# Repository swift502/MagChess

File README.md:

# MagChess

Magnetic chess game interpreter and PGN exporter for the Lego [Traditional Chess Set](https://www.lego.com/en-cz/product/traditional-chess-set-40719). Python app for the Raspberry Pi, and an Astro website to serve the results and show a leaderboard.

## App

**Setup:**

```bash
rpi_install.sh
```

After installation, a reboot is required for the I2C data rate change to take effect.

**Run:**

```bash
rpi_run.sh
```

### Desktop shortcut

```ini
[Desktop Entry]
Type=Application
Name=MagChess
Icon=/home/pi/Documents/Github/MagChess/app/assets/icon.ico
Exec=/home/pi/Documents/Github/MagChess/app/rpi_run.sh
Category=Game
```

### Autostart config

```bash
mkdir -p ~/.config/autostart
nano ~/.config/autostart/magchess.desktop
```

## Hardware

The PCB in `kicad/pcb` is designed to fit a modified underside of the lego chessboard construction found in `bricklink_studio/chessboard.io`.

The PCB needs the following components soldered onto it:

- 64x SS49E
- 4x CD74HC4067
- ADS1015
- MP1584EN

Each lego chess piece has to be fitted with a magnet on the bottom. Round 5x2mm magnets happen to fit perfectly into the bottom of each piece.

Magnet polarity is important, if white pieces read magnetic north, black pieces should be flipped and read south. The hall sensors will then read colors as positive/negative voltage, which gives the app enough information to interpret chess moves correctly.

The app should be installed on a Raspberry Pi. The chessboard draws 5V and GND from the pi. Data pins are the I2C SDA and SCL pins and four mux selection pins, by default D21, D20, D16 and D12. An estimated 800mA is drawn by the hall sensors when powered.

## Scoreboard

<div align="center">
    <a href="https://swift502.github.io/MagChess">https://swift502.github.io/MagChess</a>
</div>
<br>

Astro website showing a leaderboard and a PGN archive. Deployed via GitHub Pages.

### Build notes

```bash
npm install
npm run dev
npm run build
```

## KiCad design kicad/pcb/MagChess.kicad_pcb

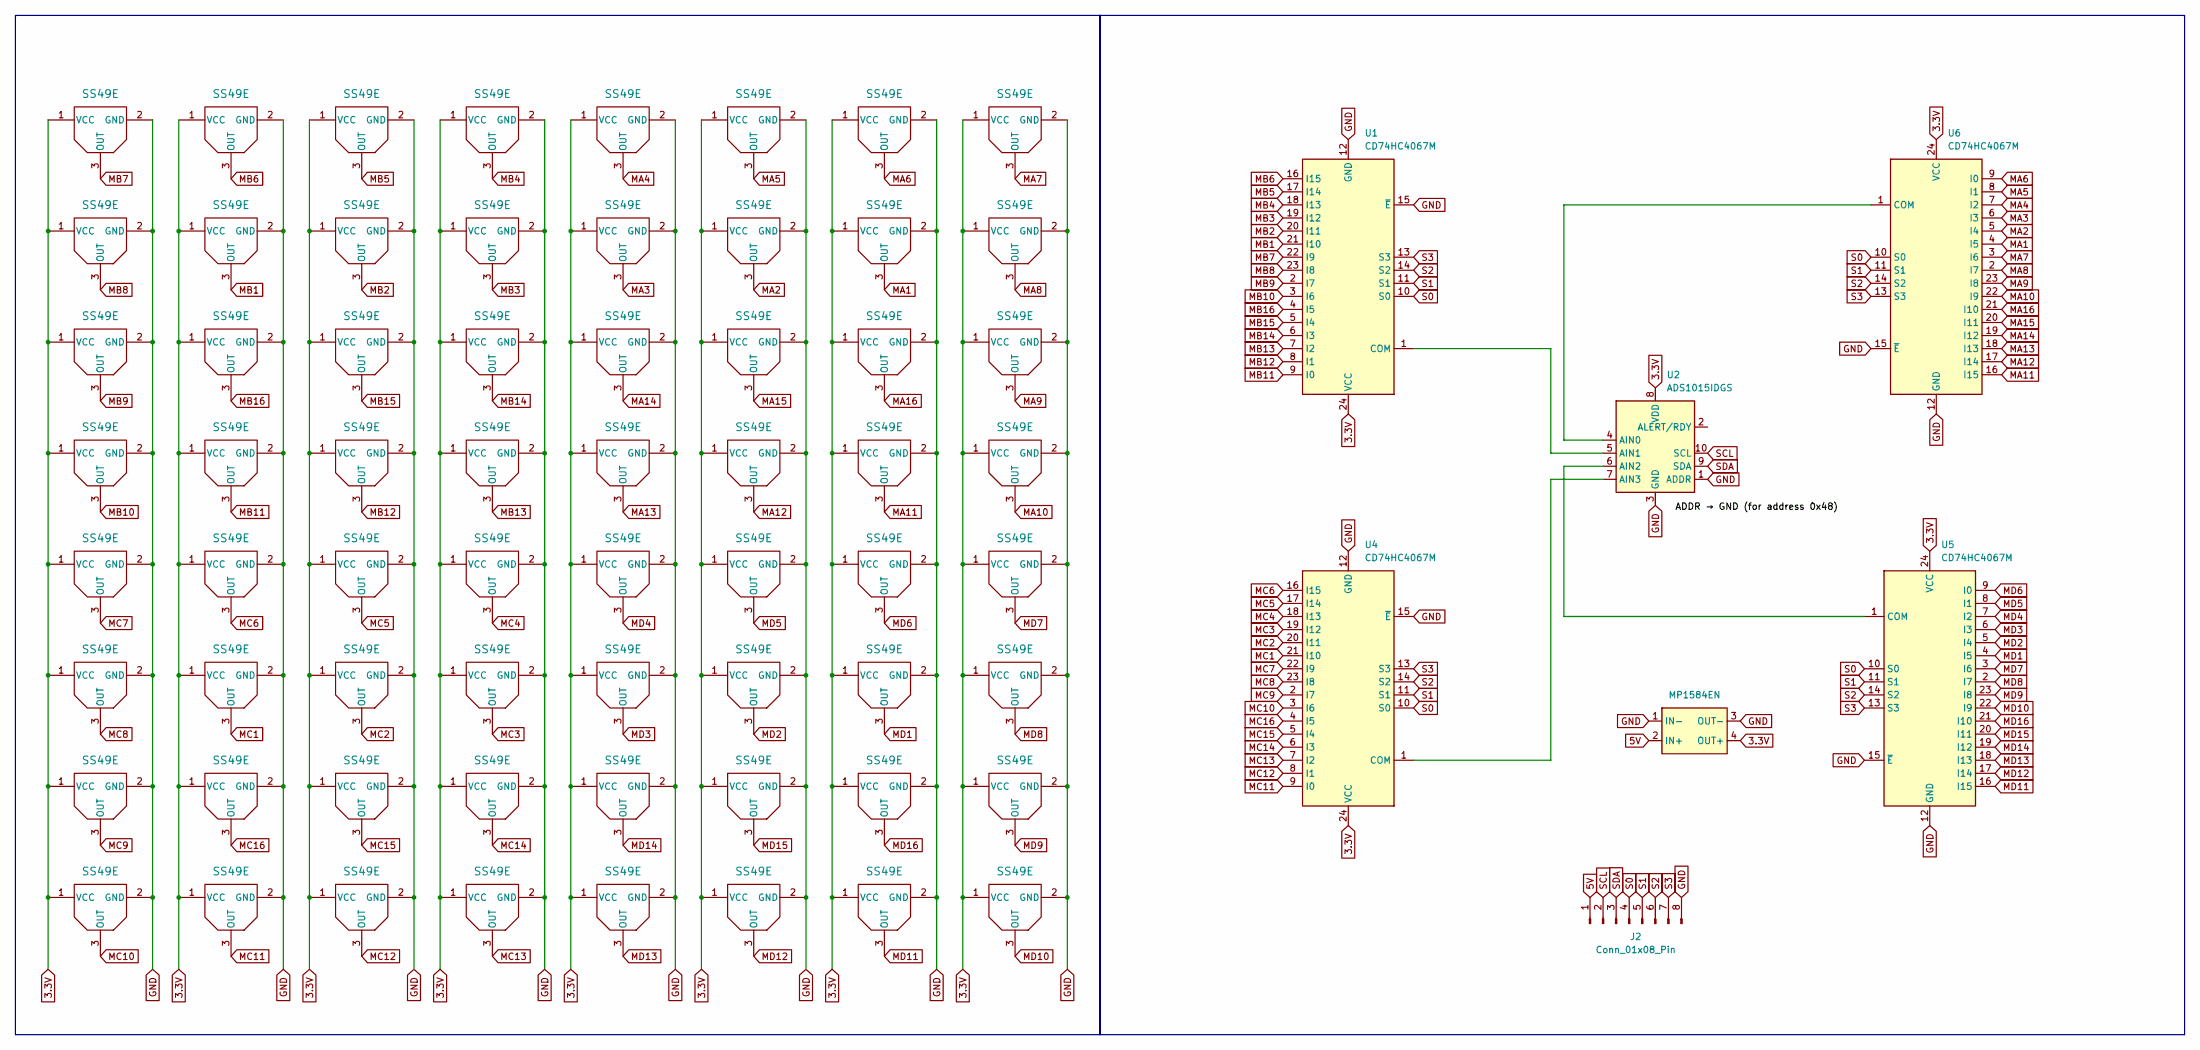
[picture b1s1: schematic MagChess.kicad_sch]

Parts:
J2: Conn_01x08_Pin; PinHeader_1x08_P2.54mm_Vertical
U1, U4, U5, U6: CD74HC4067M; CD74HC4067
U2: ADS1015IDGS; ADS1015
U3: MP1584EN; MP1584
U12, U13, U14, U15, U16, U17, U18, U19, U20, U21, U22, U23, U24, U25, U26, U27, U28, U29, U30, U31, U32, U33, U34, U35, U36, U37, U38, U39, U40, U41, U42, U43, U44, U45, U46, U47, U48, U49, U50, U51, U52, U53, U54, U55, U56, U57, U58, U59, U60, U61, U62, U63, U64, U65, U66, U67, U68, U69, U70, U71, U72, U73, U74, U75: SS49E

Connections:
3.3V: U1.24 (VCC), U2.8 (VDD), U3.4 (OUT+), U4.24 (VCC), U5.24 (VCC), U6.24 (VCC), U12.1 (VCC), U13.1 (VCC), U14.1 (VCC), U15.1 (VCC), U16.1 (VCC), U17.1 (VCC), U18.1 (VCC), U19.1 (VCC), U20.1 (VCC), U21.1 (VCC), U22.1 (VCC), U23.1 (VCC), U24.1 (VCC), U25.1 (VCC), U26.1 (VCC), U27.1 (VCC), U28.1 (VCC), U29.1 (VCC), U30.1 (VCC), U31.1 (VCC), U32.1 (VCC), U33.1 (VCC), U34.1 (VCC), U35.1 (VCC), U36.1 (VCC), U37.1 (VCC), U38.1 (VCC), U39.1 (VCC), U40.1 (VCC), U41.1 (VCC), U42.1 (VCC), U43.1 (VCC), U44.1 (VCC), U45.1 (VCC), U46.1 (VCC), U47.1 (VCC), U48.1 (VCC), U49.1 (VCC), U50.1 (VCC), U51.1 (VCC), U52.1 (VCC), U53.1 (VCC), U54.1 (VCC), U55.1 (VCC), U56.1 (VCC), U57.1 (VCC), U58.1 (VCC), U59.1 (VCC), U60.1 (VCC), U61.1 (VCC), U62.1 (VCC), U63.1 (VCC), U64.1 (VCC), U65.1 (VCC), U66.1 (VCC), U67.1 (VCC), U68.1 (VCC), U69.1 (VCC), U70.1 (VCC), U71.1 (VCC), U72.1 (VCC), U73.1 (VCC), U74.1 (VCC), U75.1 (VCC)
5V: J2.1, U3.2 (IN+)
GND: J2.8, U1.12 (GND), U1.15 (~E), U2.1 (ADDR), U2.3 (GND), U3.1 (IN-), U3.3 (OUT-), U4.12 (GND), U4.15 (~E), U5.12 (GND), U5.15 (~E), U6.12 (GND), U6.15 (~E), U12.2 (GND), U13.2 (GND), U14.2 (GND), U15.2 (GND), U16.2 (GND), U17.2 (GND), U18.2 (GND), U19.2 (GND), U20.2 (GND), U21.2 (GND), U22.2 (GND), U23.2 (GND), U24.2 (GND), U25.2 (GND), U26.2 (GND), U27.2 (GND), U28.2 (GND), U29.2 (GND), U30.2 (GND), U31.2 (GND), U32.2 (GND), U33.2 (GND), U34.2 (GND), U35.2 (GND), U36.2 (GND), U37.2 (GND), U38.2 (GND), U39.2 (GND), U40.2 (GND), U41.2 (GND), U42.2 (GND), U43.2 (GND), U44.2 (GND), U45.2 (GND), U46.2 (GND), U47.2 (GND), U48.2 (GND), U49.2 (GND), U50.2 (GND), U51.2 (GND), U52.2 (GND), U53.2 (GND), U54.2 (GND), U55.2 (GND), U56.2 (GND), U57.2 (GND), U58.2 (GND), U59.2 (GND), U60.2 (GND), U61.2 (GND), U62.2 (GND), U63.2 (GND), U64.2 (GND), U65.2 (GND), U66.2 (GND), U67.2 (GND), U68.2 (GND), U69.2 (GND), U70.2 (GND), U71.2 (GND), U72.2 (GND), U73.2 (GND), U74.2 (GND), U75.2 (GND)
MA1: U6.4 (I5), U21.3 (OUT)
MA2: U6.5 (I4), U31.3 (OUT)
MA3: U6.6 (I3), U32.3 (OUT)
MA4: U6.7 (I2), U29.3 (OUT)
MA5: U6.8 (I1), U28.3 (OUT)
MA6: U6.9 (I0), U20.3 (OUT)
MA7: U6.3 (I6), U12.3 (OUT)
MA8: U6.2 (I7), U13.3 (OUT)
MA9: U6.23 (I8), U14.3 (OUT)
MA10: U6.22 (I9), U15.3 (OUT)
MA11: U6.16 (I15), U23.3 (OUT)
MA12: U6.17 (I14), U37.3 (OUT)
MA13: U6.18 (I13), U38.3 (OUT)
MA14: U6.19 (I12), U35.3 (OUT)
MA15: U6.20 (I11), U34.3 (OUT)
MA16: U6.21 (I10), U22.3 (OUT)
MB1: U1.21 (I10), U56.3 (OUT)
MB2: U1.20 (I11), U55.3 (OUT)
MB3: U1.19 (I12), U33.3 (OUT)
MB4: U1.18 (I13), U30.3 (OUT)
MB5: U1.17 (I14), U52.3 (OUT)
MB6: U1.16 (I15), U53.3 (OUT)
MB7: U1.22 (I9), U54.3 (OUT)
MB8: U1.23 (I8), U57.3 (OUT)
MB9: U1.2 (I7), U60.3 (OUT)
MB10: U1.3 (I6), U63.3 (OUT)
MB11: U1.9 (I0), U62.3 (OUT)
MB12: U1.8 (I1), U61.3 (OUT)
MB13: U1.7 (I2), U39.3 (OUT)
MB14: U1.6 (I3), U36.3 (OUT)
MB15: U1.5 (I4), U58.3 (OUT)
MB16: U1.4 (I5), U59.3 (OUT)
MC1: U4.21 (I10), U68.3 (OUT)
MC2: U4.20 (I11), U67.3 (OUT)
MC3: U4.19 (I12), U45.3 (OUT)
MC4: U4.18 (I13), U42.3 (OUT)
MC5: U4.17 (I14), U64.3 (OUT)
MC6: U4.16 (I15), U65.3 (OUT)
MC7: U4.22 (I9), U66.3 (OUT)
MC8: U4.23 (I8), U69.3 (OUT)
MC9: U4.2 (I7), U72.3 (OUT)
MC10: U4.3 (I6), U75.3 (OUT)
MC11: U4.9 (I0), U74.3 (OUT)
MC12: U4.8 (I1), U73.3 (OUT)
MC13: U4.7 (I2), U51.3 (OUT)
MC14: U4.6 (I3), U48.3 (OUT)
MC15: U4.5 (I4), U70.3 (OUT)
MC16: U4.4 (I5), U71.3 (OUT)
MD1: U5.4 (I5), U25.3 (OUT)
MD2: U5.5 (I4), U43.3 (OUT)
MD3: U5.6 (I3), U44.3 (OUT)
MD4: U5.7 (I2), U41.3 (OUT)
MD5: U5.8 (I1), U40.3 (OUT)
MD6: U5.9 (I0), U24.3 (OUT)
MD7: U5.3 (I6), U16.3 (OUT)
MD8: U5.2 (I7), U17.3 (OUT)
MD9: U5.23 (I8), U18.3 (OUT)
MD10: U5.22 (I9), U19.3 (OUT)
MD11: U5.16 (I15), U27.3 (OUT)
MD12: U5.17 (I14), U49.3 (OUT)
MD13: U5.18 (I13), U50.3 (OUT)
MD14: U5.19 (I12), U47.3 (OUT)
MD15: U5.20 (I11), U46.3 (OUT)
MD16: U5.21 (I10), U26.3 (OUT)
unnamed: U1.1 (COM), U2.5 (AIN1)
unnamed: U2.4 (AIN0), U6.1 (COM)
unnamed: U2.6 (AIN2), U5.1 (COM)
unnamed: U2.7 (AIN3), U4.1 (COM)
S0: J2.4, U1.10 (S0), U4.10 (S0), U5.10 (S0), U6.10 (S0)
S1: J2.5, U1.11 (S1), U4.11 (S1), U5.11 (S1), U6.11 (S1)
S2: J2.6, U1.14 (S2), U4.14 (S2), U5.14 (S2), U6.14 (S2)
S3: J2.7, U1.13 (S3), U4.13 (S3), U5.13 (S3), U6.13 (S3)
SCL: J2.2, U2.10 (SCL)
SDA: J2.3, U2.9 (SDA)

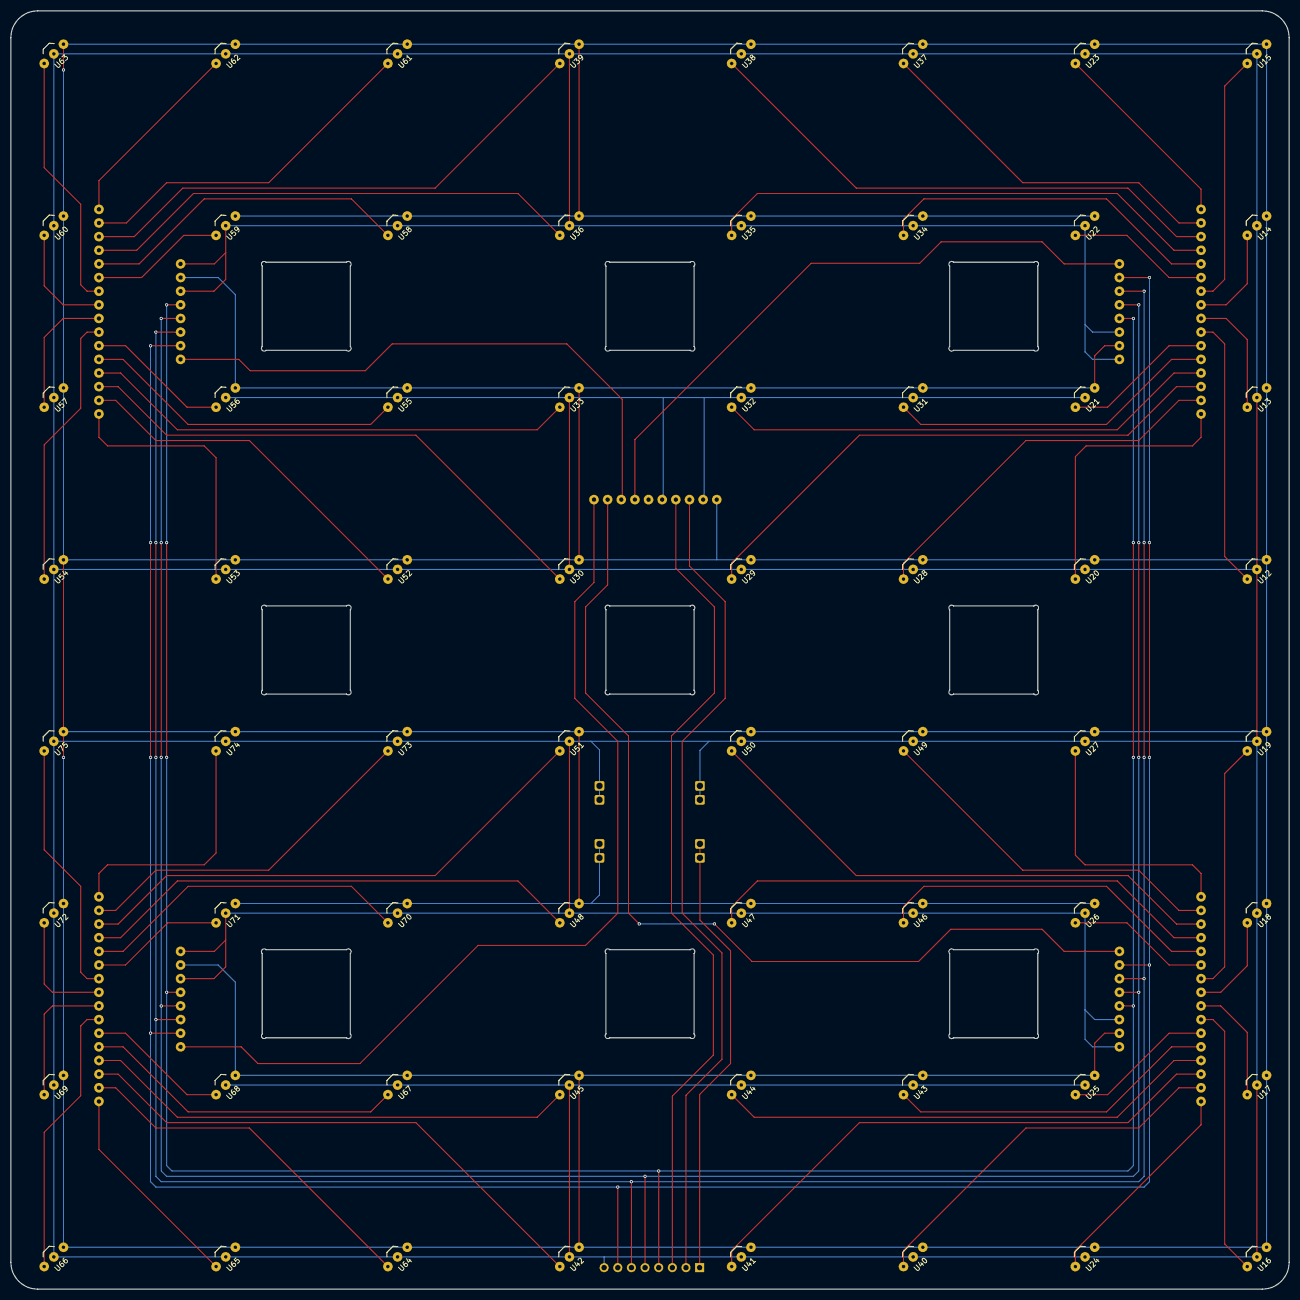
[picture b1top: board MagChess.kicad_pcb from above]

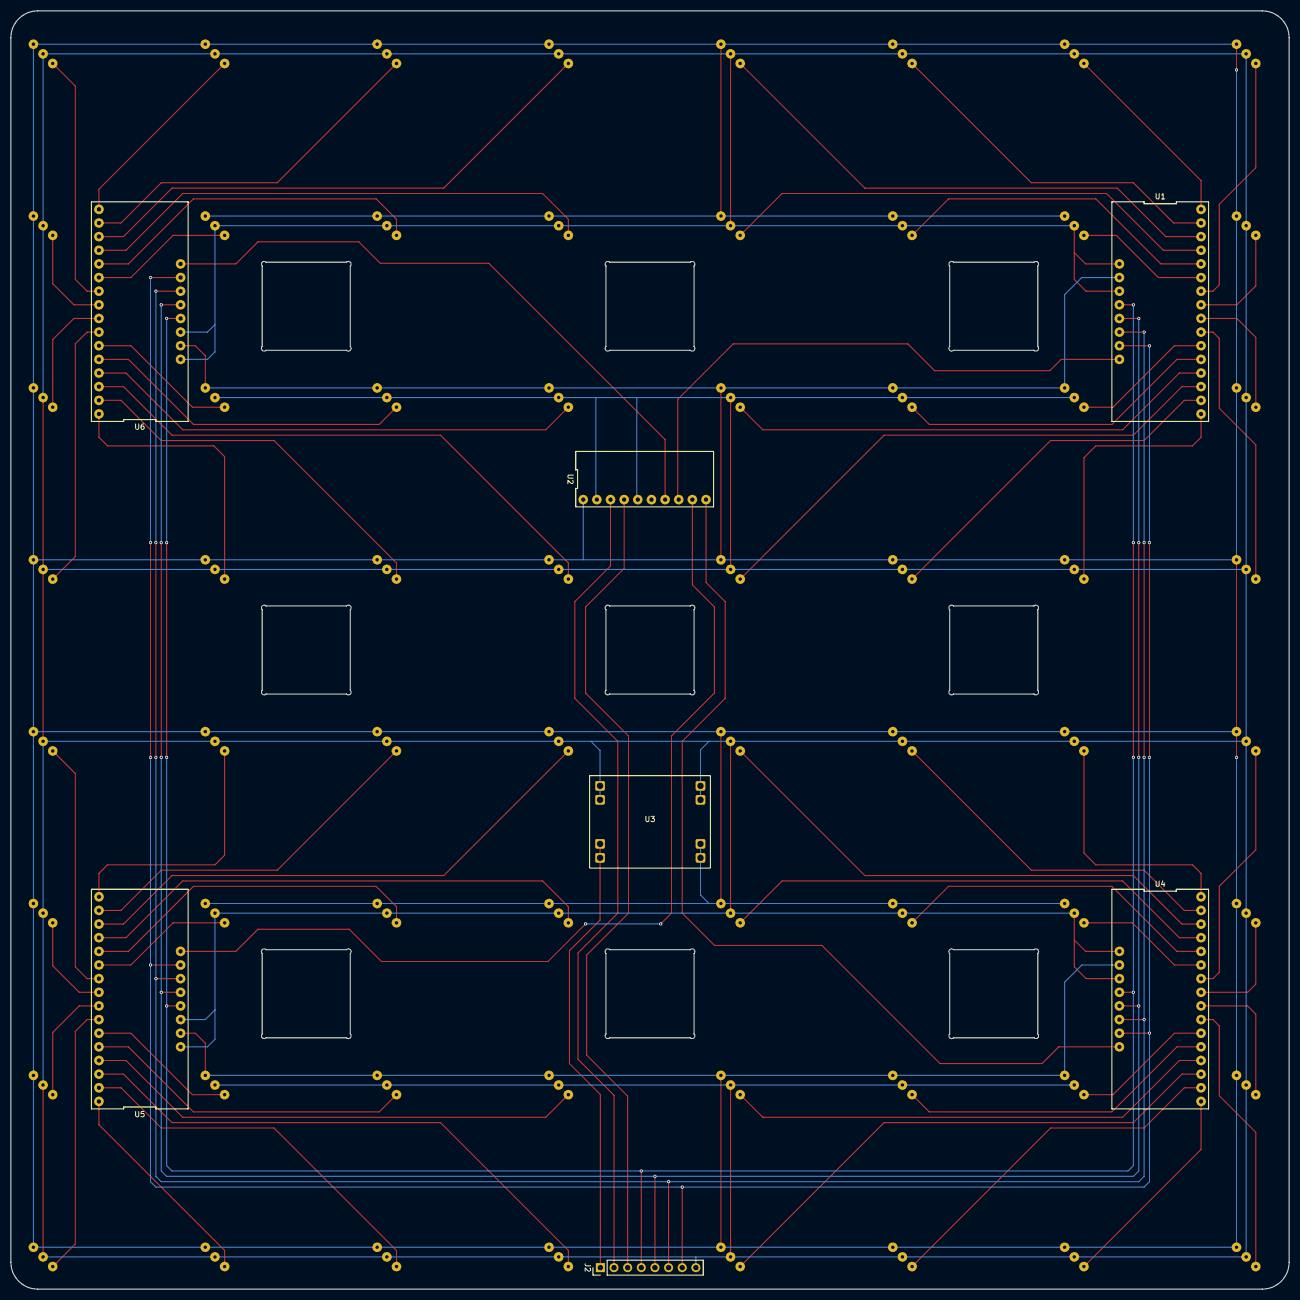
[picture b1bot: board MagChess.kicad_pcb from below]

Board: 2 copper layers, 238.0 x 238.0 mm, 71 parts (7 on the bottom side), 77 nets.

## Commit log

2025-08-14 brick link studio chess board
2025-08-15 kicad
2025-08-15 labels
2025-08-15 sensors
2025-08-15 sensor connections
2025-08-15 footprint
2025-08-15 SS49E footprint
2025-08-15 ignore
2025-08-15 libraries
2025-08-15 footprints
2025-08-15 fixes
2025-08-15 board
2025-08-15 MP1584
2025-08-15 MP1584 2
2025-08-15 positions
2025-08-15 errors fix
2025-08-15 routes 1
2025-08-16 routes 2
2025-08-16 fill zone
2025-08-16 routing v2
2025-08-16 input port
2025-08-16 PSU remake
2025-08-16 cleanup
2025-08-16 dogbone
2025-08-16 sensor silkscreen footprint
2025-08-17 board 2
2025-08-19 ADC footprint
2025-08-20 restructuring
2025-08-20 model
2025-08-20 gitignore
2025-08-20 model edit
2025-08-20 parts update
2025-08-21 assets
2025-08-21 pieces 1
2025-08-21 pieces 2
2025-08-21 piece scale
2025-08-22 replay button style
2025-08-22 style
2025-08-22 refactor
2025-08-22 esc exit
2025-08-22 piece data
2025-08-22 sensors, debug mode
2025-08-22 sensor rewrite
2025-08-22 sensor appearance
2025-08-22 icon data
2025-08-23 sensor input
2025-08-23 piece
2025-08-23 state checking
2025-08-23 dynamic spawn
2025-08-23 staging
2025-08-23 move screen
2025-08-24 hw sensor preparation
2025-08-24 icons
2025-08-24 icons 2
2025-08-24 sensor state strings
2025-08-24 imports
2025-08-24 icons 3
2025-08-24 valid move checking
2025-08-24 committing v1
2025-08-24 committing v2
2025-08-24 sensor interaction
2025-08-25 promotion, castling
2025-08-25 en passant
2025-08-25 en passant v2
2025-08-25 outcome
2025-08-25 check
2025-08-25 winning fix
2025-08-26 constants
2025-08-26 async sensors 1
2025-08-26 async sensors 2
2025-08-26 flags
2025-08-26 callback cleanup
2025-08-27 mapping
2025-08-27 mapping 2
2025-08-27 flipping v1
2025-08-27 move screen v2
2025-08-27 copy PGN
2025-08-27 tap ui
2025-08-27 replay button refresh
2025-08-27 interaction mask
2025-08-28 3.11
2025-08-28 rpi scripts
2025-08-28 split overlay
2025-08-28 advantage bar spring
2025-08-28 status updates fix
2025-08-28 icon
2025-08-28 game review v1
2025-08-28 show state fix
2025-08-29 snackbar color, sensor data None checking
2025-08-29 opacity
2025-08-29 Create LICENSE
2025-08-29 advantage v1
2025-08-29 ratings v1
2025-08-29 ratings v2
2025-08-30 depth
2025-08-30 hw update
2025-08-30 engine flag
2025-08-30 rotation
2025-08-30 better reporting, rotation 2
2025-08-31 info display
2025-08-31 flipping improvements
2025-08-31 calibration 1
2025-08-31 calibration 2
2025-08-31 show_state fix, page update optimization
2025-08-31 calibration SPS
2025-09-01 formatting
2025-09-01 rpi custom build
2025-09-01 sort
2025-09-01 data rate
2025-09-01 readme
2025-09-01 Disable smoothing
2025-09-01 remove stockfish
2025-09-01 text rotation
2025-09-01 rpi detection
2025-09-01 detection 2
2025-09-01 detection 3
2025-09-01 calibration flag
2025-09-01 improvements
2025-09-01 magic detection v1
2025-09-01 calibration fix
2025-09-01 unified state stack, en passant improvements
2025-09-01 even better en passant
2025-09-02 font
2025-09-02 install update
2025-09-02 sensor speed
2025-09-02 fix rpi_run
2025-09-02 revert delay
2025-09-02 info messages
2025-09-02 Update LICENSE
2025-09-03 bash
2025-09-03 theme
2025-09-03 revert
2025-09-03 info improvements
2025-09-03 notifications vs messages
2025-09-03 images
2025-09-03 tweaks
2025-09-04 gists update
2025-09-04 comments
2025-09-04 type fix
2025-09-06 Players tab
2025-09-06 Add PGN headers and player selection functionality
2025-09-06 requirements fix
2025-09-07 point to players branch
2025-09-08 folder
2025-09-08 docs test
2025-09-08 example update
2025-09-09 unpublish
2025-09-09 scoreboard test
2025-09-09 test
2025-09-09 structure 1
2025-09-10 name
2025-09-10 data init
2025-09-10 reaadme
2025-09-10 responsive
2025-09-10 favicon
2025-09-10 dates, sorting
2025-09-10 column width
2025-09-10 structure
2025-09-10 all players
2025-09-10 lenient game over
2025-09-10 rename
2025-09-10 structure 2
2025-09-10 dialog v1
2025-09-10 commit part 1
2025-09-10 desc
2025-09-11 committing
2025-09-11 App highlight upload 2025-09-11T09:46:49
2025-09-11 App game upload 2025-09-11T09:47:33
2025-09-11 final touches
2025-09-11 no game checks
2025-09-11 permissions
2025-09-11 App highlight upload 2025-09-11 11:43:52
2025-09-11 sort highlights
2025-09-11 players add
2025-09-11 leaderboard logic
2025-09-11 App game upload 2025-09-11 12:25:21
2025-09-11 leaderboard refactor
2025-09-11 names
2025-09-11 links
2025-09-11 styles
2025-09-11 show player names
2025-09-11 git push raise if error
2025-09-11 image
2025-09-11 App game upload 2025-09-11 15:52:19
2025-09-11 order fix
2025-09-11 App game upload 2025-09-11 16:17:19
2025-09-11 move count
2025-09-11 App game upload 2025-09-11 16:37:21
2025-09-11 App game upload 2025-09-11 16:37:34
2025-09-11 fail safe
2025-09-11 better comparison
2025-09-11 date formatting
2025-09-11 scoreboard css v2
2025-09-11 base
2025-09-11 icons fix
2025-09-11 colors
2025-09-12 App game upload 2025-09-12 14:44:03
2025-09-12 format
2025-09-12 leaderboard logic rewrite
2025-09-12 ranks
2025-11-15 image 2
2025-11-15 image 3
2025-11-15 image 4
2025-11-15 image 5
2025-11-16 image 6
2025-11-16 image 7
